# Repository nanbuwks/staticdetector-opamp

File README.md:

# staticdetector

OpenSource hardware Static Electricity Detector (OPAMP version)

We developed this product for soldering practice.

- It can be assembled with only a few parts.
- Low cost
- Designed with surface mounting.

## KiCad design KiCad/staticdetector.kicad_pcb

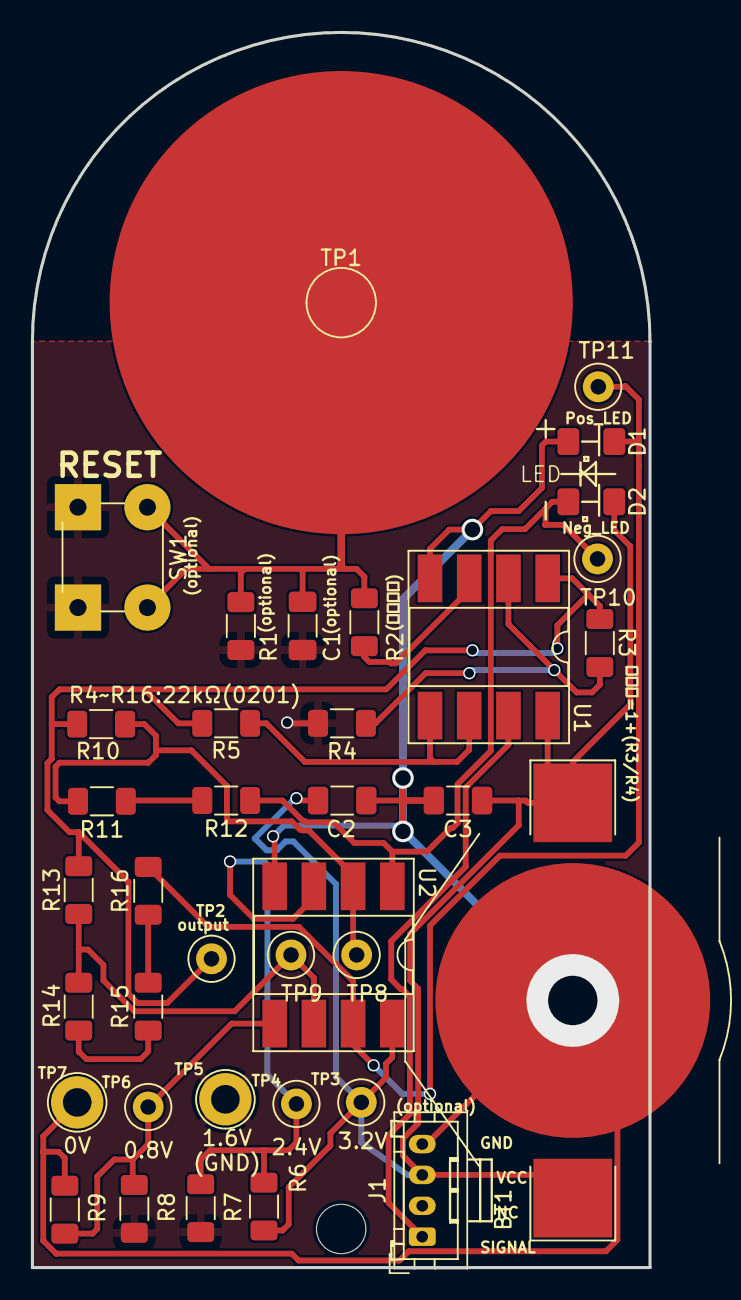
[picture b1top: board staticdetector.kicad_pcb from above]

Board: 2 copper layers, 40.0 x 80.0 mm, 37 parts (0 on the bottom side), 18 nets.

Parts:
BT1: Battery_Cell; BatteryHolder_Keystone_3002_1x2032
C1, C2, C3: 100n; C_1206_3216Metric_Pad1.33x1.80mm_HandSolder
D1: Negative Vf=3V; LED_1206_3216Metric_Pad1.42x1.75mm_HandSolder
D2: Positive Vf=2V; LED_1206_3216Metric_Pad1.42x1.75mm_HandSolder
J1: HY_CONN; JST_PH_B4B-PH-K_1x04_P2.00mm_Vertical
R1: 20M; R_1206_3216Metric_Pad1.30x1.75mm_HandSolder
R2: 100k; R_1206_3216Metric_Pad1.30x1.75mm_HandSolder
R3: 1M; R_1206_3216Metric_Pad1.30x1.75mm_HandSolder
R4, R5, R6, R7, R8, R9, R10, R11, R12, R13, R14, R15, R16: 22k; R_1206_3216Metric_Pad1.30x1.75mm_HandSolder
SW1: SW_Push; SW_PUSH_6mm
TP1: ProveAntena; TestPoint_Pad_D4.0mm
TP2, TP10, TP11: output; TestPoint_Loop_D1.80mm_Drill1.0mm_Beaded
TP3: 3.2V; TestPoint_Loop_D1.80mm_Drill1.0mm_Beaded
TP4, TP8: 2.4V; TestPoint_Loop_D1.80mm_Drill1.0mm_Beaded
TP5: 1.6V; TestPoint_Loop_D2.50mm_Drill1.85mm
TP6, TP9: 0.8V; TestPoint_Loop_D1.80mm_Drill1.0mm_Beaded
TP7: 0V; TestPoint_Loop_D2.50mm_Drill1.85mm
U1, U2: AD8506; DIP-8_W8.89mm_SMDSocket_LongPads

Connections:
+VDC: BT1.1 (+), C2.1, C3.1, D2.2 (A), J1.3, R6.1, TP3.1, U1.8 (V+), U2.8 (V+)
-VDC: BT1.2 (-), C2.2, C3.2, D1.1 (K), J1.4, R9.2, TP7.1, U1.4 (V-), U2.4 (V-)
GND: C1.2, R1.2, R4.2, R7.2, R8.1, SW1.2, TP5.1
unnamed: C1.1, R1.1, R2.1, SW1.1, TP1.1
unnamed: D1.2 (A), R16.2, TP11.1, U2.7
unnamed: D2.1 (K), R12.1, TP10.1, U2.1
unnamed: J1.1, U1.7
unnamed: R3.2, R5.1, R10.1, R13.1, TP2.1, U1.1
unnamed: R11.1, R12.2
unnamed: R14.2, R15.1
unnamed: R15.2, R16.1
unnamed: R2.2, U1.3 (+)
unnamed: R3.1, R4.1, U1.2 (-)
unnamed: R5.2, U1.5 (+), U1.6 (-)
unnamed: R6.2, R7.1, TP4.1, U2.3 (+)
unnamed: R10.2, R11.2, TP8.1, U2.2 (-)
unnamed: R8.2, R9.1, TP6.1, U2.5 (+)
unnamed: R13.2, R14.1, TP9.1, U2.6 (-)

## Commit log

2023-04-14 change README
2023-04-14 fork from staticdetector
2023-04-14 change file to OPAMP version
2023-04-14 change schematics
